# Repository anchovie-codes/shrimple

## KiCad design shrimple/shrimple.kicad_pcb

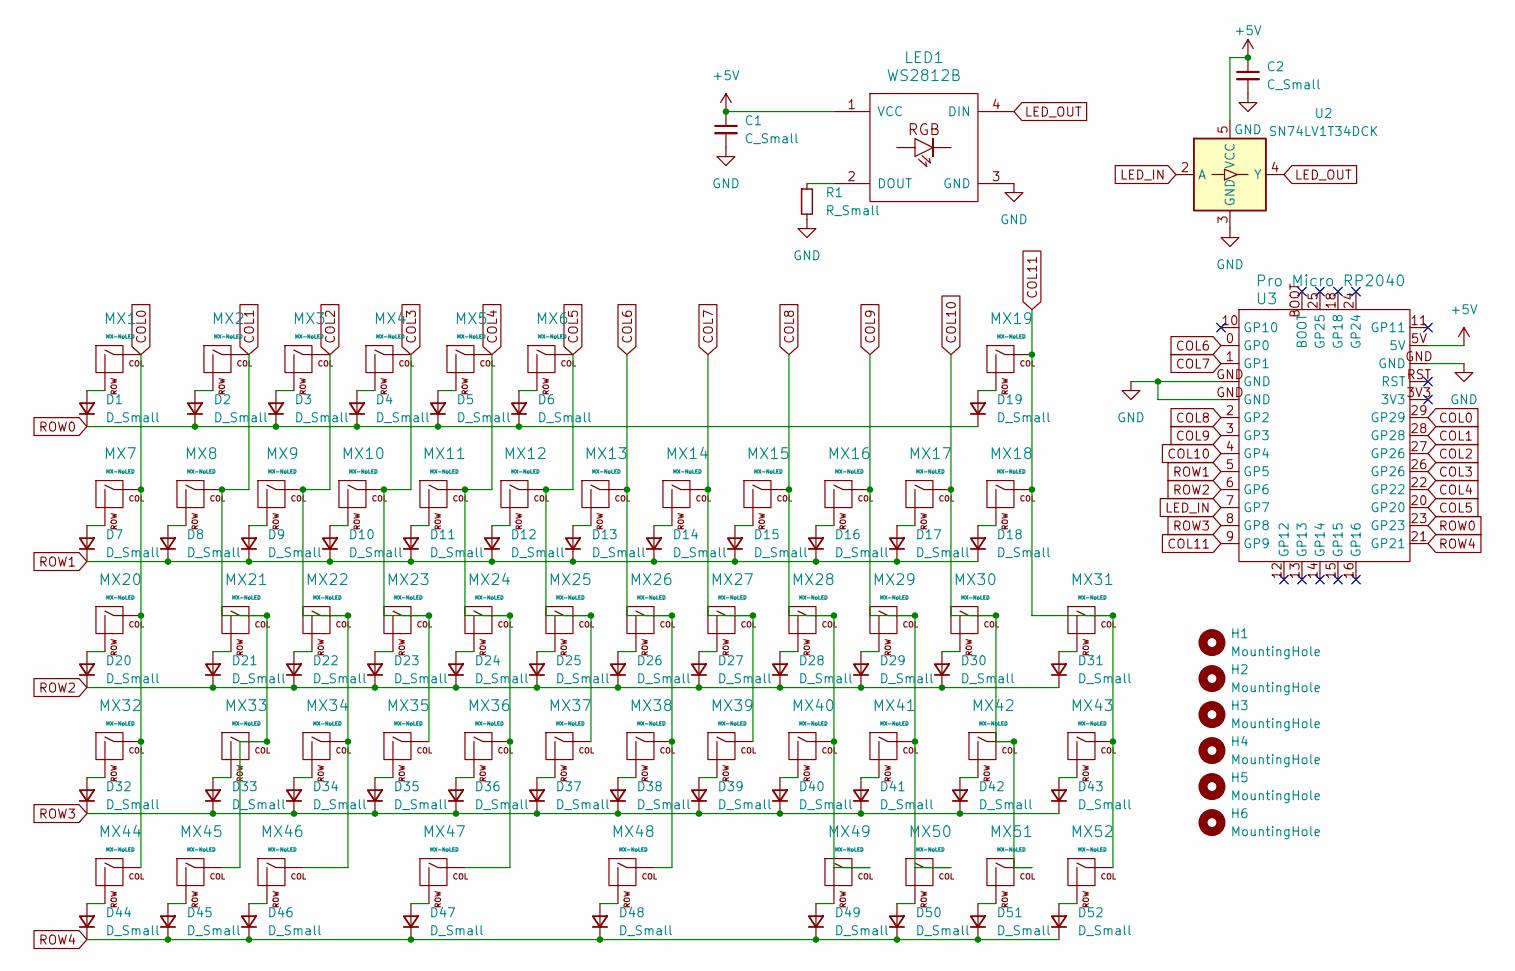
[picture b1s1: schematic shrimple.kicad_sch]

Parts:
C1, C2: C_Small; C_0603_1608Metric_Pad1.08x0.95mm_HandSolder
D1, D2, D3, D4, D5, D6, D7, D8, D9, D10, D11, D12, D13, D14, D15, D16, D17, D18, D19, D20, D21, D22, D23, D24, D25, D26, D27, D28, D29, D30, D31, D32, D33, D34, D35, D36, D37, D38, D39, D40, D41, D42, D43, D44, D45, D46, D47, D48, D49, D50, D51, D52: D_Small; D_SOD-123
H1, H2, H3, H4, H5, H6: MountingHole; MountingHole_2.2mm_M2_Pad_TopOnly
LED1: WS2812B
MX1, MX2, MX3, MX4, MX5, MX6, MX7, MX8, MX9, MX10, MX11, MX12, MX13, MX14, MX15, MX16, MX17, MX18, MX19, MX21, MX22, MX23, MX24, MX25, MX26, MX27, MX28, MX29, MX30, MX33, MX34, MX35, MX36, MX37, MX38, MX39, MX40, MX41, MX43, MX45, MX49, MX50, MX51, MX52: MX-NoLED; MX-Solderable-1U
MX20, MX42, MX44, MX46: MX-NoLED; MX-Solderable-1.25U
MX31, MX32: MX-NoLED; MX-Solderable-1.75U
MX47: MX-NoLED; MX-Solderable-2.25U-ReversedStabilizers
MX48: MX-NoLED; MX-Solderable-2.75U-ReversedStabilizers
R1: R_Small; R_0805_2012Metric_Pad1.20x1.40mm_HandSolder
U2: SN74LV1T34DCK; SOT-353_SC-70-5
U3: Pro Micro RP2040; pro_micro_rp2040

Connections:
+5V: C1.1, C2.1, LED1.1 (VCC), U2.5 (VCC), U3.5V
COL0: MX1.1 (COL), MX7.1 (COL), MX20.1 (COL), MX32.1 (COL), MX44.1 (COL), U3.29 (GP29)
COL1: MX2.1 (COL), MX8.1 (COL), MX21.1 (COL), MX33.1 (COL), MX45.1 (COL), U3.28 (GP28)
COL2: MX3.1 (COL), MX9.1 (COL), MX22.1 (COL), MX34.1 (COL), MX46.1 (COL), U3.27 (GP26)
COL3: MX4.1 (COL), MX10.1 (COL), MX23.1 (COL), MX35.1 (COL), U3.26 (GP26)
COL4: MX5.1 (COL), MX11.1 (COL), MX24.1 (COL), MX36.1 (COL), MX47.1 (COL), U3.22 (GP22)
COL5: MX6.1 (COL), MX12.1 (COL), MX25.1 (COL), MX37.1 (COL), U3.20 (GP20)
COL6: MX13.1 (COL), MX26.1 (COL), MX38.1 (COL), MX48.1 (COL), U3.0 (GP0)
COL7: MX14.1 (COL), MX27.1 (COL), MX39.1 (COL), U3.1 (GP1)
COL8: MX15.1 (COL), MX28.1 (COL), MX40.1 (COL), MX49.1 (COL), U3.2 (GP2)
COL9: MX16.1 (COL), MX29.1 (COL), MX41.1 (COL), MX50.1 (COL), U3.3 (GP3)
COL10: MX17.1 (COL), MX30.1 (COL), MX42.1 (COL), MX51.1 (COL), U3.4 (GP4)
COL11: MX18.1 (COL), MX19.1 (COL), MX31.1 (COL), MX43.1 (COL), MX52.1 (COL), U3.9 (GP9)
GND: C1.2, C2.2, LED1.3 (GND), R1.2, U2.3 (GND), U3.GND
LED_IN: U2.2 (A), U3.7 (GP7)
LED_OUT: LED1.4 (DIN), U2.4 (Y)
unnamed: D1.2 (A), MX1.2 (ROW)
unnamed: D2.2 (A), MX2.2 (ROW)
unnamed: D3.2 (A), MX3.2 (ROW)
unnamed: D4.2 (A), MX4.2 (ROW)
unnamed: D5.2 (A), MX5.2 (ROW)
unnamed: D6.2 (A), MX6.2 (ROW)
unnamed: D7.2 (A), MX7.2 (ROW)
unnamed: D8.2 (A), MX8.2 (ROW)
unnamed: D9.2 (A), MX9.2 (ROW)
unnamed: D10.2 (A), MX10.2 (ROW)
unnamed: D11.2 (A), MX11.2 (ROW)
unnamed: D12.2 (A), MX12.2 (ROW)
unnamed: D13.2 (A), MX13.2 (ROW)
unnamed: D14.2 (A), MX14.2 (ROW)
unnamed: D15.2 (A), MX15.2 (ROW)
unnamed: D16.2 (A), MX16.2 (ROW)
unnamed: D17.2 (A), MX17.2 (ROW)
unnamed: D18.2 (A), MX18.2 (ROW)
unnamed: D19.2 (A), MX19.2 (ROW)
unnamed: D20.2 (A), MX20.2 (ROW)
unnamed: D21.2 (A), MX21.2 (ROW)
unnamed: D22.2 (A), MX22.2 (ROW)
unnamed: D23.2 (A), MX23.2 (ROW)
unnamed: D24.2 (A), MX24.2 (ROW)
unnamed: D25.2 (A), MX25.2 (ROW)
unnamed: D26.2 (A), MX26.2 (ROW)
unnamed: D27.2 (A), MX27.2 (ROW)
unnamed: D28.2 (A), MX28.2 (ROW)
unnamed: D29.2 (A), MX29.2 (ROW)
unnamed: D30.2 (A), MX30.2 (ROW)
unnamed: D31.2 (A), MX31.2 (ROW)
unnamed: D32.2 (A), MX32.2 (ROW)
unnamed: D33.2 (A), MX33.2 (ROW)
unnamed: D34.2 (A), MX34.2 (ROW)
unnamed: D35.2 (A), MX35.2 (ROW)
unnamed: D36.2 (A), MX36.2 (ROW)
unnamed: D37.2 (A), MX37.2 (ROW)
unnamed: D38.2 (A), MX38.2 (ROW)
unnamed: D39.2 (A), MX39.2 (ROW)
unnamed: D40.2 (A), MX40.2 (ROW)
unnamed: D41.2 (A), MX41.2 (ROW)
unnamed: D42.2 (A), MX42.2 (ROW)
unnamed: D43.2 (A), MX43.2 (ROW)
unnamed: D44.2 (A), MX44.2 (ROW)
unnamed: D45.2 (A), MX45.2 (ROW)
unnamed: D46.2 (A), MX46.2 (ROW)
unnamed: D47.2 (A), MX47.2 (ROW)
unnamed: D48.2 (A), MX48.2 (ROW)
unnamed: D49.2 (A), MX49.2 (ROW)
unnamed: D50.2 (A), MX50.2 (ROW)
unnamed: D51.2 (A), MX51.2 (ROW)
unnamed: D52.2 (A), MX52.2 (ROW)
unnamed: LED1.2 (DOUT), R1.1
ROW0: D1.1 (K), D2.1 (K), D3.1 (K), D4.1 (K), D5.1 (K), D6.1 (K), D19.1 (K), U3.23 (GP23)
ROW1: D7.1 (K), D8.1 (K), D9.1 (K), D10.1 (K), D11.1 (K), D12.1 (K), D13.1 (K), D14.1 (K), D15.1 (K), D16.1 (K), D17.1 (K), D18.1 (K), U3.5 (GP5)
ROW2: D20.1 (K), D21.1 (K), D22.1 (K), D23.1 (K), D24.1 (K), D25.1 (K), D26.1 (K), D27.1 (K), D28.1 (K), D29.1 (K), D30.1 (K), D31.1 (K), U3.6 (GP6)
ROW3: D32.1 (K), D33.1 (K), D34.1 (K), D35.1 (K), D36.1 (K), D37.1 (K), D38.1 (K), D39.1 (K), D40.1 (K), D41.1 (K), D42.1 (K), D43.1 (K), U3.8 (GP8)
ROW4: D44.1 (K), D45.1 (K), D46.1 (K), D47.1 (K), D48.1 (K), D49.1 (K), D50.1 (K), D51.1 (K), D52.1 (K), U3.21 (GP21)

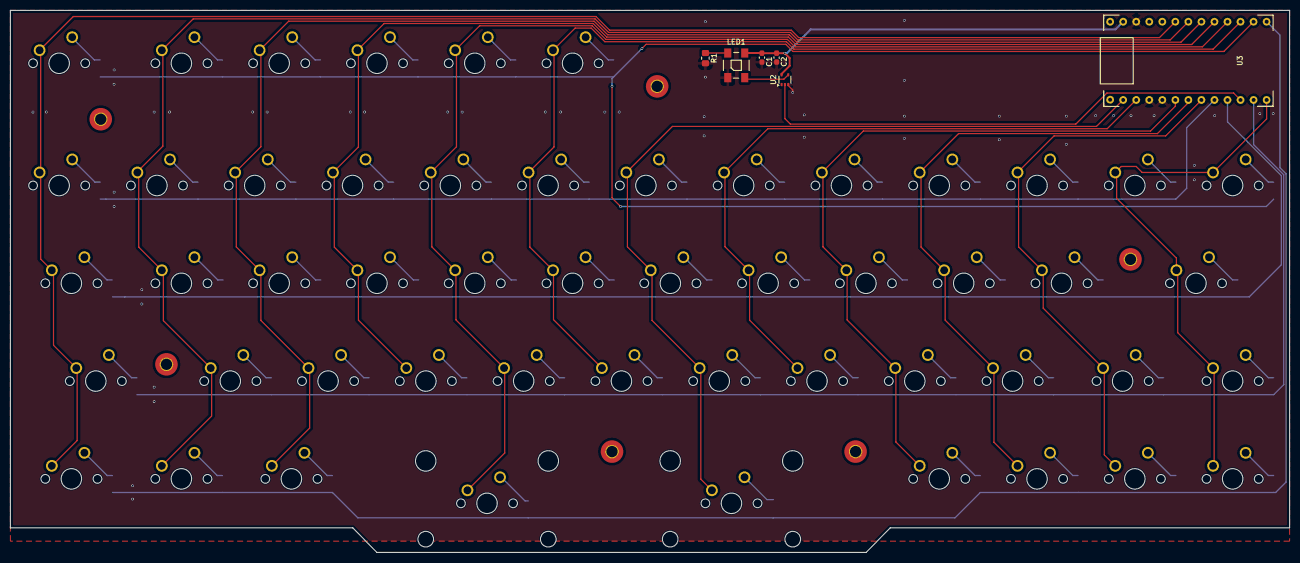
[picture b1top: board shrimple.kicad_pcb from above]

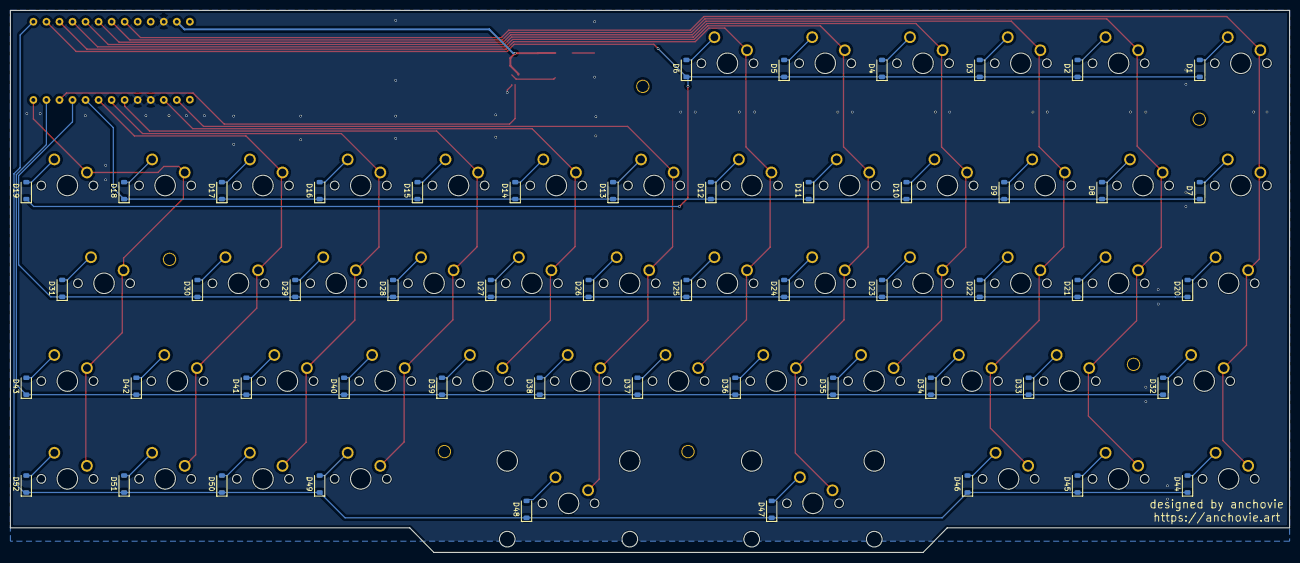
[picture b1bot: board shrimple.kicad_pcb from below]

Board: 2 copper layers, 249.2 x 105.6 mm, 116 parts (52 on the bottom side), 74 nets.

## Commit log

2025-01-15 instantiated kicad schematic
2025-01-18 updated schematic and placed footprints
2025-01-19 added LED circuit
2025-01-19 added LED, routing attempt the first
2025-01-19 added ground fills and vias
2025-01-20 added art
2025-01-20 fixed art and weird row trace
2025-01-20 gerbers
2025-01-21 initialized firmware
2025-01-22 updated keymap and layer names
2025-01-25 fixed spacebar placement fuck my stupid baka life
2025-01-26 moved mounting holes
2025-01-27 moved MCU, rerouted
2025-01-28 changed mcu to aliexpress pro micro
2025-01-29 debugged firmware, added case parts
2025-01-31 updated parts list, fixed firmware pin assignment
2025-01-31 Squashed commit of the following:
    commit 14746e2b2c2fbb4b60cdda4e7e5a03e42a6594c3
    Author: anchovie-codes <littlebrother.free@gmail.com>
    Date: Fri Jan 31 13:08:23 2025 -0500
    updated parts list, fixed firmware pin assignment
    commit 23731c4664425e572959f773be3c9afba22b46e0
    Author: anchovie-codes <littlebrother.free@gmail.com>
2025-01-31 flipped mcu and rerouted
2025-02-01 redesigned case files
2025-02-04 updated case STEPs and drawings
2025-02-07 updated weight design and drawings
2025-02-07 fixed matrix bugs
2025-02-07 carried over matrix bug fixes in main
2025-02-12 updated drawing mid
2025-02-14 added level shifter
2025-02-14 fixed layout, added level shifter, made gerbers
2025-02-14 moved mounting hole, updated gerbers
2025-02-14 updated firmware gpio and layout
2025-02-14 Squashed commit of the following:
    commit 0917563cd294cf20495b95da51ce8923af6e95fb
    Author: anchovie-codes <littlebrother.free@gmail.com>
    Date: Fri Feb 14 11:46:37 2025 -0500
    updated firmware gpio and layout
    commit 7b5bbbd23beed7ff01c20b44607d9c6e08a5b151
    Author: anchovie-codes <littlebrother.free@gmail.com>
2025-02-14 updated switchplate to new layout
2025-02-15 fixed plate and upper tolerances
2025-02-15 cleaned up directory, rebuilt drawings
2025-03-07 organized filesystem, removed outdated assets
